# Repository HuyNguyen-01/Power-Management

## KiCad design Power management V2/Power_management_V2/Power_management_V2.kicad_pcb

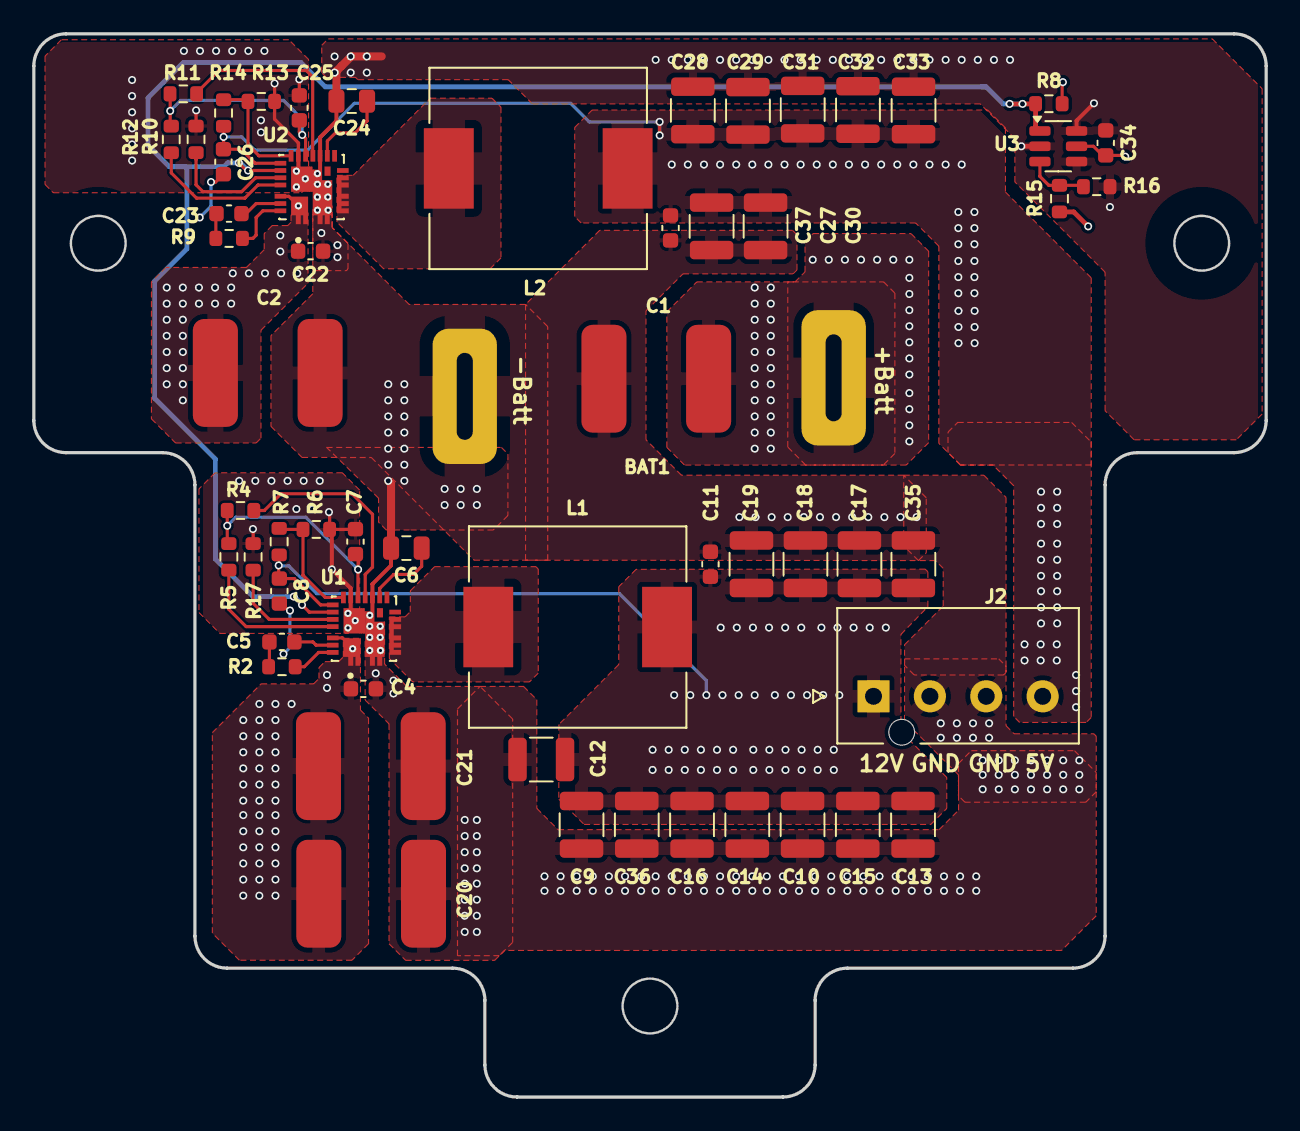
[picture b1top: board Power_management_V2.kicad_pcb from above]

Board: 4 copper layers, 76.5 x 66.0 mm, 60 parts (0 on the bottom side), 28 nets.

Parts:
BAT1: Conn_01x02; Milwaukee 18V battery connector R1
C1, C2, C20, C21: 22u/50V/3025; C_CER_7.5x6.3
C4, C5, C8, C11, C22, C23, C26, C34, C37: 100n/50V/0603; C_0603_1608Metric
C6, C24: 4.7u/50V/0805; C_0805_2012Metric
C7, C25: 1u/50V/0603; C_0603_1608Metric
C9, C10, C12, C13, C14, C15, C16, C17, C18, C19, C27, C28, C29, C30, C31, C32, C33, C35, C36: 22u/25V/1210; C_1210_3225Metric
J2: 1722861104; MOLEX_1722861104
L1, L2: 2.2u/22A; IND_SRP1265A-2R2M
NT1, NT2: NetTie_2; NetTie-2_SMD_Pad1.56mm
R2, R9: 2.2R/0603; R_0603_1608Metric
R4, R5, R8, R11, R12: 100k/0603; R_0603_1608Metric
R6, R13: 10k/0603/0.1%; R_0603_1608Metric
R7: 191K/0603/0.1%; R_0603_1608Metric
R10, R17: 200k/0603; R_0603_1608Metric
R14: 73.2K/0603/0.1; R_0603_1608Metric
R15: 2M/0603; R_0603_1608Metric
R16: 51.1K/0603; R_0603_1608Metric
U1, U2: SIC437AED; VREG_SIC437AED-T1-GE3
U3: TPS3711DDCR; TSOT-23-6

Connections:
+BATT: BAT1.1, C1.1, C2.1, C4.2, C20.1, C21.1, C22.2, C34.2, R8.2, R15.2, U1.1 (VIN), U1.22 (VIN), U2.1 (VIN), U2.22 (VIN), U3.5 (VDD)
/12V/EN_12V: R8.1, U1.19 (EN), U2.19 (EN), U3.1 (OUT)
/+5V: C26.2, C27.1, C28.1, C29.1, C30.1, C31.1, C32.1, C33.1, C37.2, J2.4, L2.2, R14.2, U2.18 (VOUT)
/+12V: C8.2, C9.1, C10.1, C11.2, C12.1, C13.1, C14.1, C15.1, C16.1, C17.1, C18.1, C19.1, C35.1, C36.1, J2.1, L1.2, R7.2, U1.18 (VOUT)
GND: BAT1.2, C1.2, C2.2, C4.1, C6.2, C8.1, C9.2, C10.2, C11.1, C12.2, C13.2, C14.2, C15.2, C16.2, C17.2, C18.2, C19.2, C20.2, C21.2, C22.1, C24.2, C26.1, C27.2, C28.2, C29.2, C30.2, C31.2, C32.2, C33.2, C34.1, C35.2, C36.2, C37.1, J2.2, J2.3, NT1.2, NT2.2, R16.1, U1.3 (PGND), U1.13 (PGND), U2.3 (PGND), U2.13 (PGND), U3.2 (GND-2), U3.4 (GND-4), U3.6 (GND-6)
GND1: C25.2, NT1.1, R10.2, R13.1, U2.16 (AGND), U2.25 (AGND)
GND2: C7.2, NT2.1, R6.1, R17.2, U1.16 (AGND), U1.25 (AGND)
unnamed: C5.2, R2.2
unnamed: C23.2, R9.2
unnamed: L1.1, U1.5 (SW)
unnamed: L2.1, U2.5 (SW)
unnamed: C5.1, U1.23 (BOOT)
unnamed: R6.2, R7.1, U1.17 (FB)
unnamed: R5.2, U1.21 (MODE1)
unnamed: R17.1, U1.20 (MODE2)
unnamed: R4.1, U1.14 (PGOOD)
unnamed: R2.1, U1.24 (PHASE)
unnamed: C7.1, R4.2, R5.1, U1.15 (VDD)
unnamed: C6.1, U1.12 (VDRV)
unnamed: C23.1, U2.23 (BOOT)
unnamed: R13.2, R14.1, U2.17 (FB)
unnamed: R12.2, U2.21 (MODE1)
unnamed: R10.1, U2.20 (MODE2)
unnamed: R11.1, U2.14 (PGOOD)
unnamed: R9.1, U2.24 (PHASE)
unnamed: C25.1, R11.2, R12.1, U2.15 (VDD)
unnamed: C24.1, U2.12 (VDRV)
unnamed: R15.1, R16.2, U3.3 (SENSE)

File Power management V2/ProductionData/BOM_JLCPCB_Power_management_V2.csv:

Designator,Quantity,Comment,Footprint,JLCPCB Part #
,,,,
"C1,C2,C20,C21",4,22u/50V/3025,Library:C_CER_7.5x6.3,C508864
"C4,C5,C8,C11,C22,C23,C26,C34,C37",9,100n/50V/0603,Capacitor_SMD:C_0603_1608Metric,C3011652
"C6,C24",2,4.7u/50V/0805,Capacitor_SMD:C_0805_2012Metric,C437557
"C7,C25",2,1u/50V/0603,Capacitor_SMD:C_0603_1608Metric,C5199872
"C9,C10,C12,C13,C14,C15,C16,C17,C18,C19,C27,C28,C29,C30,C31,C32,C33,C35,C36",19,22u/25V/1210,Capacitor_SMD:C_1210_3225Metric,C52306
J2,1,1722861104,Library:MOLEX_1722861104,C586647
"L1,L2",2,2.2u/22A,Library:IND_SRP1265A-2R2M,C2831487
,,,,
"R2,R9",2,2.2R/0603,Resistor_SMD:R_0603_1608Metric,C144672
"R4,R5,R8,R11,R12",5,100k/0603,Resistor_SMD:R_0603_1608Metric,C14675
"R6,R13",2,10k/0603/0.1%,Resistor_SMD:R_0603_1608Metric,C95204
R7,1,191K/0603/0.1%,Resistor_SMD:R_0603_1608Metric,C861179
"R10,R17",2,200k/0603,Resistor_SMD:R_0603_1608Metric,C105574
R14,1,73.2K/0603/0.1,Resistor_SMD:R_0603_1608Metric,C862276
R15,1,2M/0603,Resistor_SMD:R_0603_1608Metric,C114615
R16,1,51.1K/0603,Resistor_SMD:R_0603_1608Metric,C364359
"U1,U2",2,SIC437AED,Library:VREG_SIC437AED-T1-GE3,C2071432
U3,1,TPS3711DDCR,Package_TO_SOT_SMD:TSOT-23-6,C2877180

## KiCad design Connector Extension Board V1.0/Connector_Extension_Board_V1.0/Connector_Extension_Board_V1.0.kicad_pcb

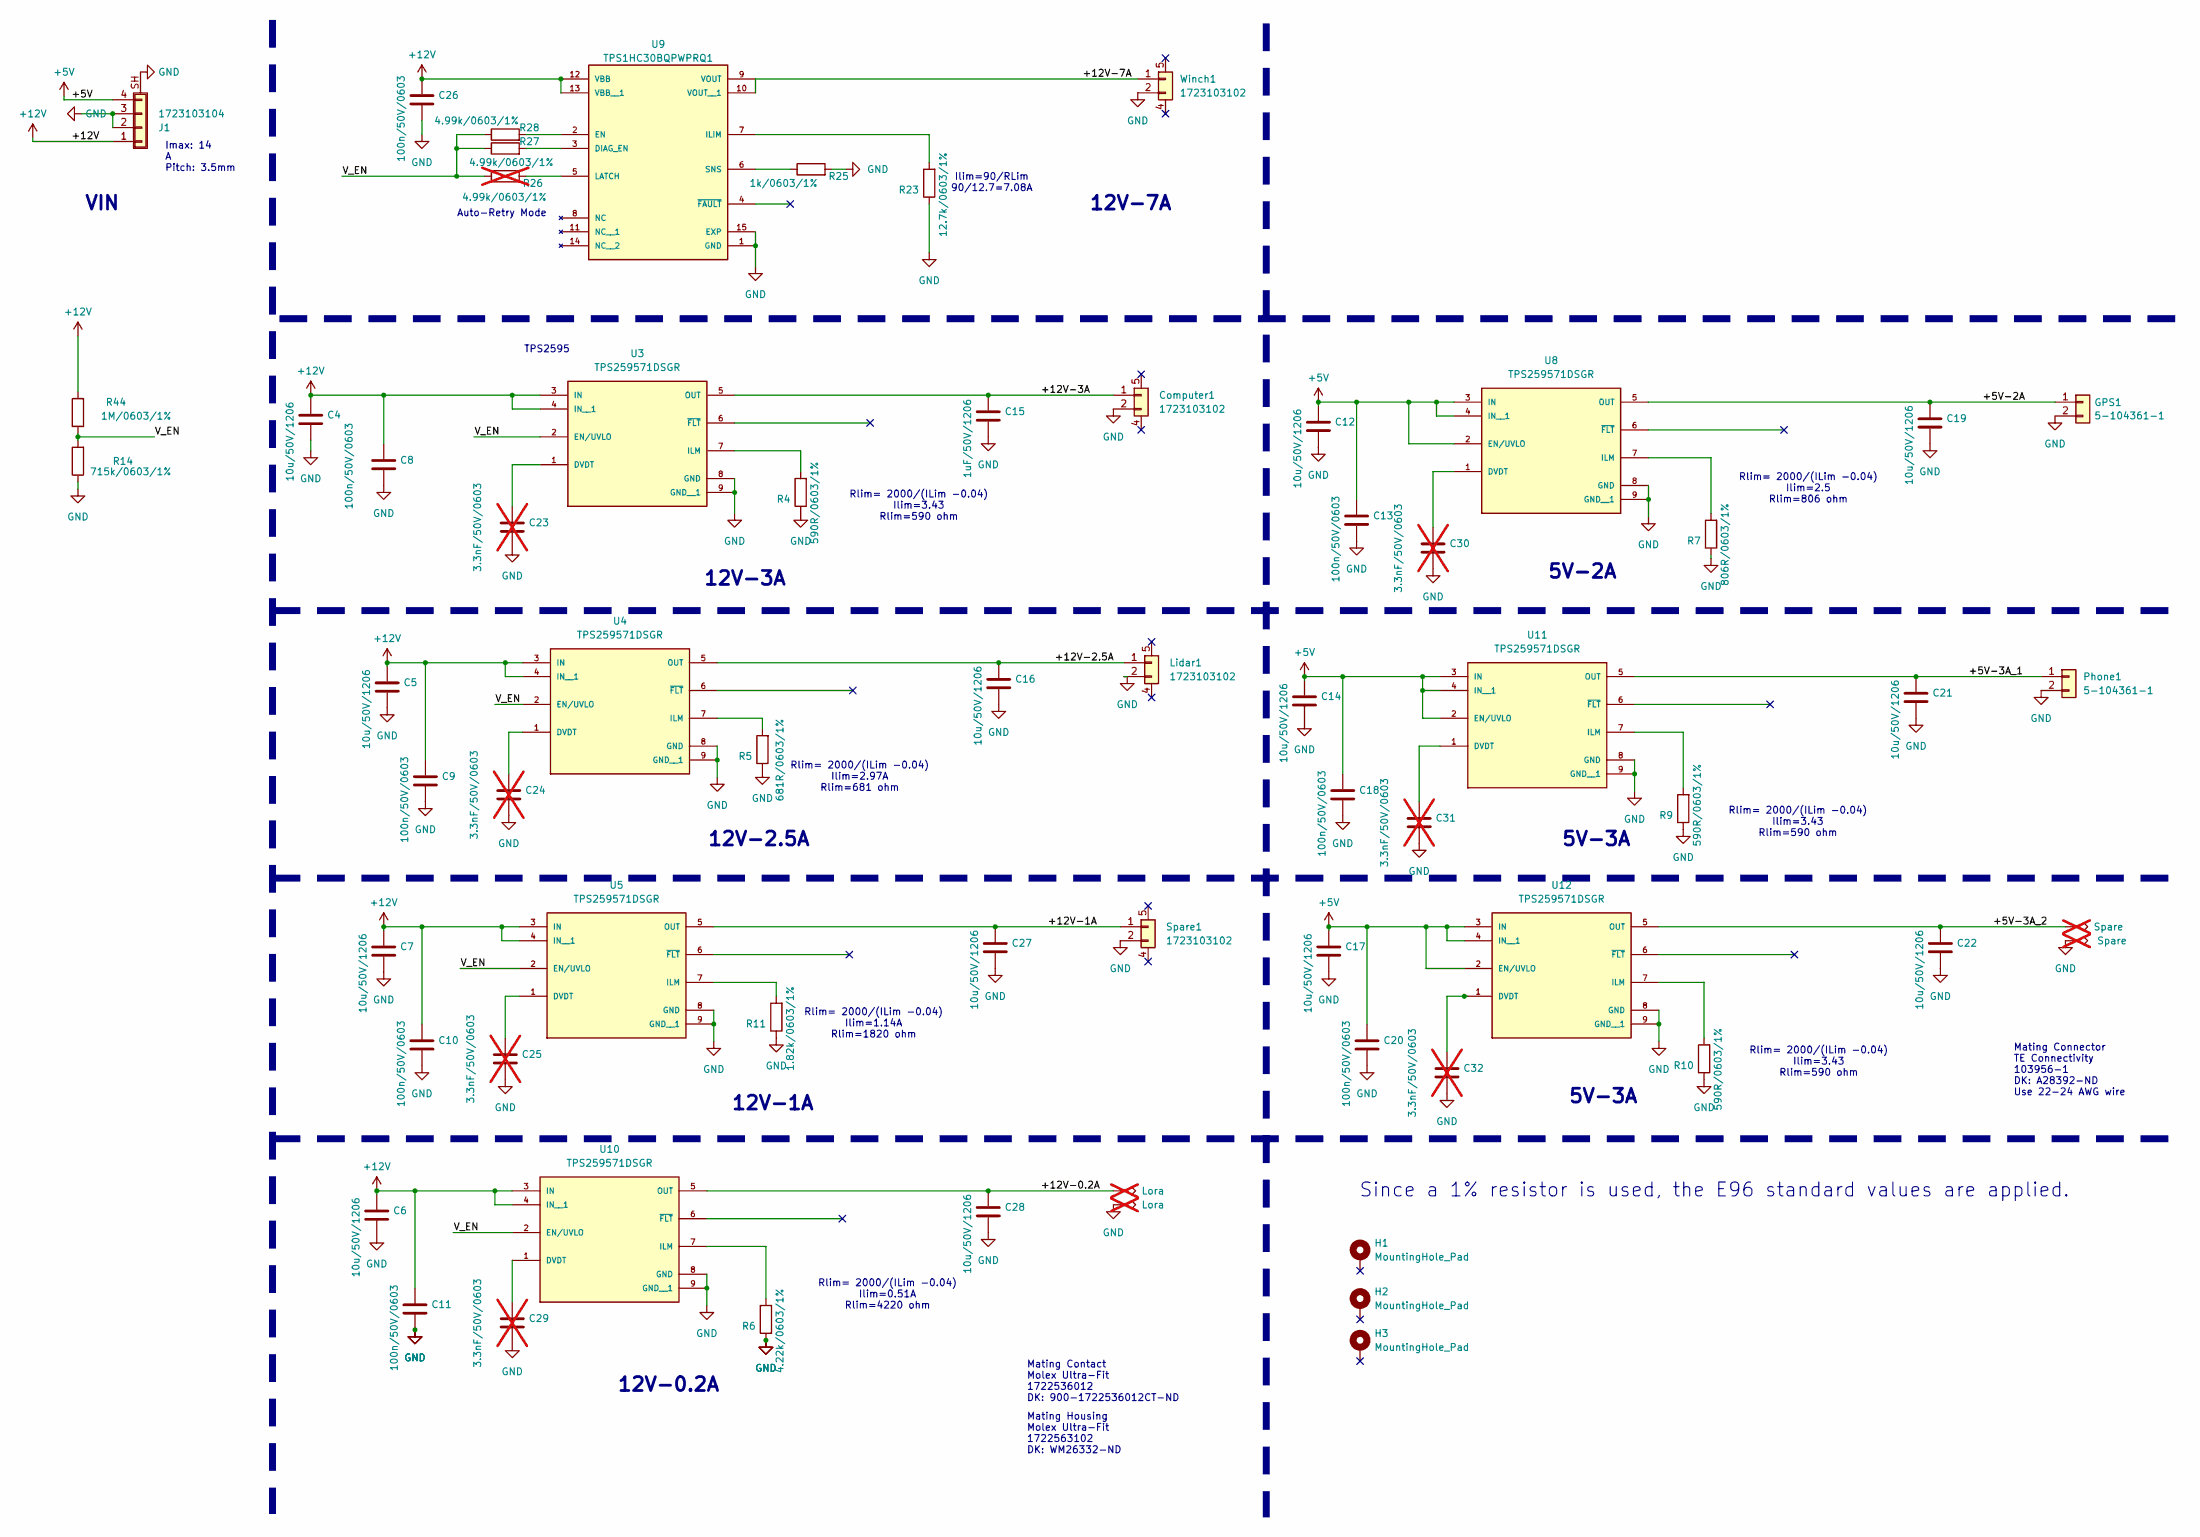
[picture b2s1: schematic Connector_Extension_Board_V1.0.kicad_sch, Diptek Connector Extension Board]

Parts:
C4, C5, C6, C7, C12, C14, C16, C17, C19, C21, C22, C27, C28: 10u/50V/1206; C_1206_3216Metric; Digikey 1276-2876-1-ND
C8, C9, C10, C11, C13, C18, C20, C26: 100n/50V/0603; C_0603_1608Metric; Digikey 587-1243-1-ND
C15: 1uF/50V/1206; C_1206_3216Metric; Digikey 1276-1068-1-ND
C23, C24, C25, C29, C30, C31, C32: 3.3nF/50V/0603; C_0603_1608Metric; Digikey NC; not fitted
Computer1: 1723103102; MOLEX_1723103102; Part 1723102202; Digikey 900-1723103102-ND
GPS1: 5-104361-1; TE_5-104361-1; Part 5-104361-1; Digikey A33961-ND
H1, H2, H3: MountingHole_Pad; MountingHole_3.1-5.8; Digikey NC
J1: 1723103104; MOLEX_1723103104; DIGIKEY 900-1723103104-ND
Lidar1: 1723103102; MOLEX_1723103102; Part 1723102202; Digikey 900-1723103102-ND
Phone1: 5-104361-1; TE_5-104361-1; Part 5-104361-1; Digikey A33961-ND
R4, R9, R10: 590R/0603/1%; R_0603_1608Metric; Digikey 311-590HRCT-ND
R5: 681R/0603/1%; R_0603_1608Metric; Digikey RMCF0603FT681RCT-ND
R6: 4.22k/0603/1%; R_0603_1608Metric; Digikey 311-4.22KHRCT-ND
R7: 806R/0603/1%; R_0603_1608Metric; Digikey P806HCT-ND
R11: 1.82k/0603/1%; R_0603_1608Metric; Digikey 311-1.82KHRCT-ND
R14: 715k/0603/1%; R_0603_1608Metric; Digikey 311-715KHRCT-ND
R23: 12.7k/0603/1%; R_0603_1608Metric; Digikey P12.7HCT-ND
R25: 1k/0603/1%; R_0603_1608Metric; Digikey RMCF0603FT1K00CT-ND
R26: 4.99k/0603/1%; R_0603_1608Metric; Digikey NC; not fitted
R27, R28: 4.99k/0603/1%; R_0603_1608Metric; Digikey RMCF0603FT4K99CT-ND
R44: 1M/0603/1%; R_0603_1608Metric; Digikey P1.00MHCT-ND
Spare1: 1723103102; MOLEX_1723103102; Part 1723102202; Digikey 900-1723103102-ND
TP1, TP2: Lora; TestPoint_Loop_D2.50mm_Drill1.0mm; not fitted
TP3, TP4: Spare; TestPoint_Loop_D2.50mm_Drill1.0mm; not fitted
U3, U4, U5, U8, U10, U11, U12: TPS259571DSGR; SON50P200X200X80-9N; DIGIKEY 296-50500-1-ND
U9: TPS1HC30BQPWPRQ1; IC_TPS1HC30BQPWPRQ1; DIGIKEY 296-TPS1HC30BQPWPRQ1CT-ND
Winch1: 1723103102; MOLEX_1723103102; Part 1723102202; Digikey 900-1723103102-ND

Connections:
+5V: C12.1, C13.1, C14.1, C17.1, C18.1, C20.1, J1.4, U8.2 (EN/UVLO), U8.3 (IN), U8.4 (IN__1), U11.2 (EN/UVLO), U11.3 (IN), U11.4 (IN__1), U12.2 (EN/UVLO), U12.3 (IN), U12.4 (IN__1)
+12V: C4.1, C5.1, C6.1, C7.1, C8.1, C9.1, C10.1, C11.1, C26.1, J1.1, R44.2, U3.3 (IN), U3.4 (IN__1), U4.3 (IN), U4.4 (IN__1), U5.3 (IN), U5.4 (IN__1), U9.12 (VBB), U9.13 (VBB__1), U10.3 (IN), U10.4 (IN__1)
/+5V-2A: C19.1, GPS1.1, U8.5 (OUT)
/+5V-3A_1: C21.1, Phone1.1, U11.5 (OUT)
/+5V-3A_2: C22.1, TP3.1, U12.5 (OUT)
/+12V-0.2A: C28.1, TP1.1, U10.5 (OUT)
/+12V-1A: C27.1, Spare1.1, U5.5 (OUT)
/+12V-2.5A: C16.1, Lidar1.1, U4.5 (OUT)
/+12V-3A: C15.1, Computer1.1, U3.5 (OUT)
/+12V-7A: U9.9 (VOUT), U9.10 (VOUT__1), Winch1.1
/V_EN: R14.2, R26.1, R27.1, R28.1, R44.1, U3.2 (EN/UVLO), U4.2 (EN/UVLO), U5.2 (EN/UVLO), U10.2 (EN/UVLO)
GND: C4.2, C5.2, C6.2, C7.2, C8.2, C9.2, C10.2, C11.2, C12.2, C13.2, C14.2, C15.2, C16.2, C17.2, C18.2, C19.2, C20.2, C21.2, C22.2, C23.2, C24.2, C25.2, C26.2, C27.2, C28.2, C29.2, C30.2, C31.2, C32.2, Computer1.2, GPS1.2, J1.2, J1.3, J1.SH (Shield), Lidar1.2, Phone1.2, R4.1, R5.1, R6.1, R7.1, R9.1, R10.1, R11.1, R14.1, R23.1, R25.2, Spare1.2, TP2.1, TP4.1, U3.8 (GND), U3.9 (GND__1), U4.8 (GND), U4.9 (GND__1), U5.8 (GND), U5.9 (GND__1), U8.8 (GND), U8.9 (GND__1), U9.1 (GND), U9.15 (EXP), U10.8 (GND), U10.9 (GND__1), U11.8 (GND), U11.9 (GND__1), U12.8 (GND), U12.9 (GND__1), Winch1.2
unnamed: C23.1, U3.1 (DVDT)
unnamed: R4.2, U3.7 (ILM)
unnamed: C24.1, U4.1 (DVDT)
unnamed: R5.2, U4.7 (ILM)
unnamed: C25.1, U5.1 (DVDT)
unnamed: R11.2, U5.7 (ILM)
unnamed: C30.1, U8.1 (DVDT)
unnamed: R7.2, U8.7 (ILM)
unnamed: R27.2, U9.3 (DIAG_EN)
unnamed: R28.2, U9.2 (EN)
unnamed: R23.2, U9.7 (ILIM)
unnamed: R26.2, U9.5 (LATCH)
unnamed: R25.1, U9.6 (SNS)
unnamed: C29.1, U10.1 (DVDT)
unnamed: R6.2, U10.7 (ILM)
unnamed: C31.1, U11.1 (DVDT)
unnamed: R9.2, U11.7 (ILM)
unnamed: C32.1, U12.1 (DVDT)
unnamed: R10.2, U12.7 (ILM)

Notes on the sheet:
5V-3A
12V-3A
Mating Connector TE Connectivity 103956-1 DK: A28392-ND Use 22-24 AWG wire
12V-1A
TPS2595
Rlim= 2000/(ILim -0.04) Ilim=1.14A Rlim=1820 ohm
Mating Housing Molex Ultra-Fit 1722563102 DK: WM26332-ND
12V-7A
Rlim= 2000/(ILim -0.04) Ilim=2.97A Rlim=681 ohm
5V-2A
12V-2.5A
Since a 1% resistor is used, the E96 standard values are applied.
Rlim= 2000/(ILim -0.04) Ilim=2.5 Rlim=806 ohm
Auto-Retry Mode
Imax: 14 A Pitch: 3.5mm
Rlim= 2000/(ILim -0.04) Ilim=3.43 Rlim=590 ohm
Mating Contact Molex Ultra-Fit 1722536012 DK: 900-1722536012CT-ND
VIN
12V-0.2A
Ilim=90/RLim 90/12.7=7.08A
Rlim= 2000/(ILim -0.04) Ilim=0.51A Rlim=4220 ohm

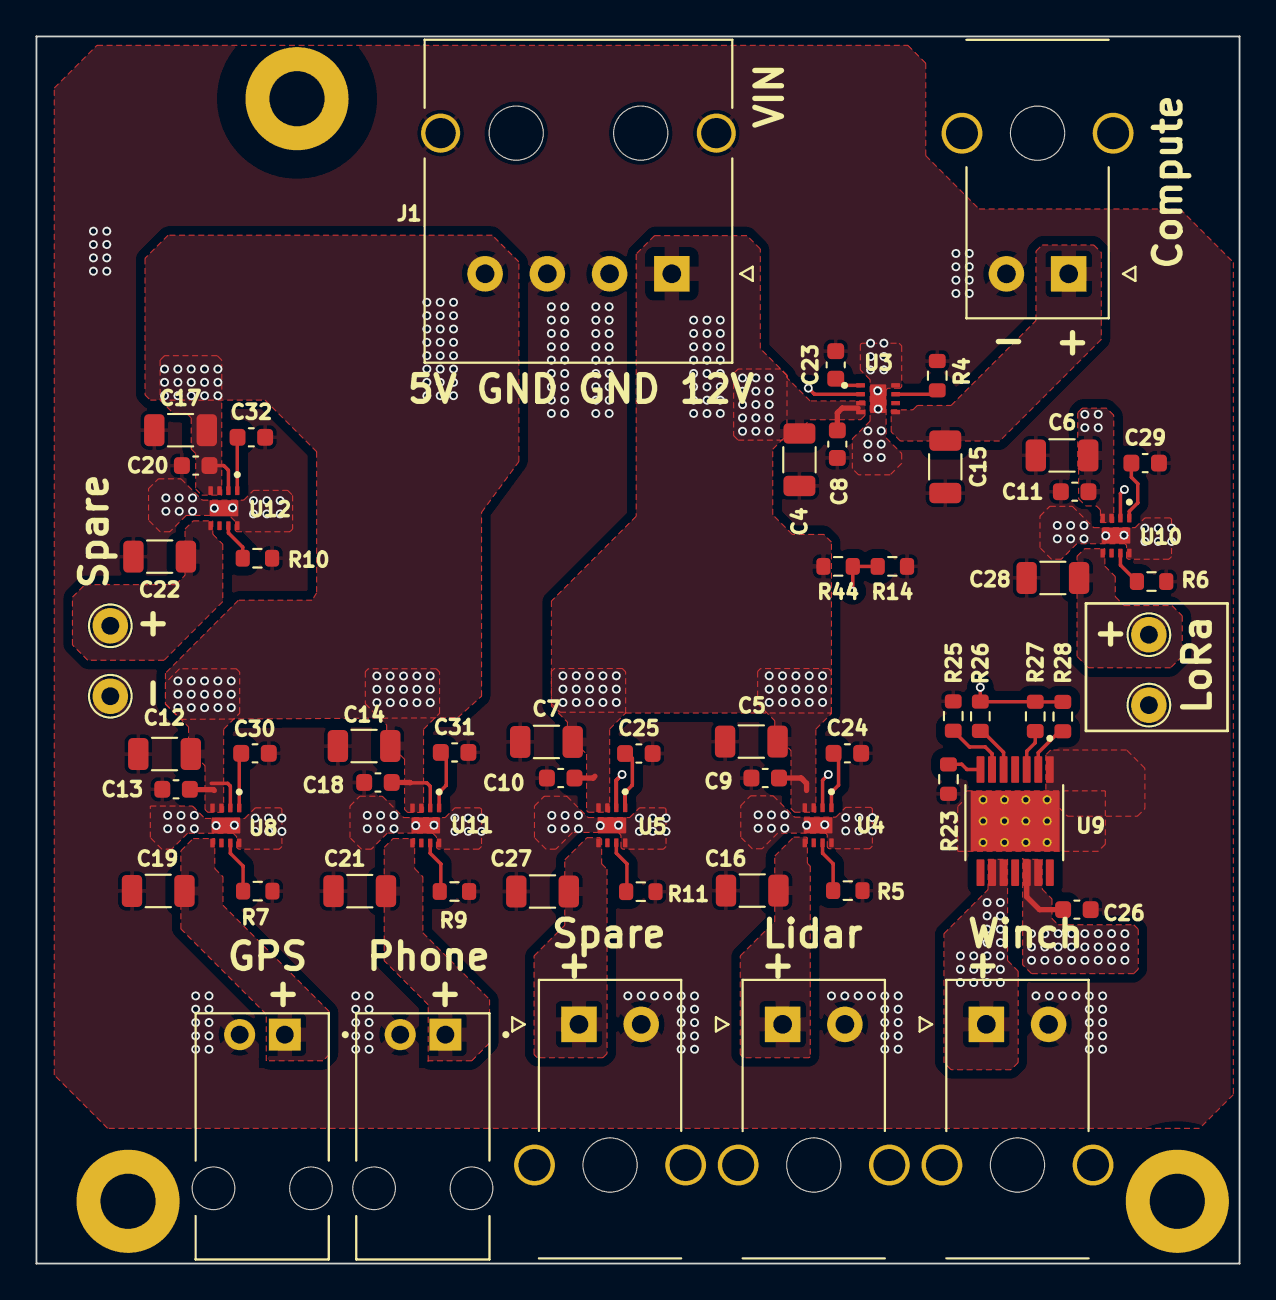
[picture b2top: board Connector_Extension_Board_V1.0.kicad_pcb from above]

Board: 4 copper layers, 67.7 x 69.0 mm, 65 parts (0 on the bottom side), 31 nets.

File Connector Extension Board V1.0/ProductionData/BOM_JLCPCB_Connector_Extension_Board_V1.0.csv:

Reference,Qty,Value,Footprint,JLCPCB Part #
"C4,C5,C6,C7,C12,C14,C16,C17,C19,C21,C22,C27,C28",13,10u/50V/1206,Capacitor_SMD:C_1206_3216Metric,C13585
"C8,C9,C10,C11,C13,C18,C20,C26",8,100n/50V/0603,Capacitor_SMD:C_0603_1608Metric,C3011652
C15,1,1uF/50V/1206,Capacitor_SMD:C_1206_3216Metric,C1848
"Computer1,Lidar1,Spare1,Winch1",4,1723103102,Library:MOLEX_1723103102,C17318087
"GPS1,Phone1",2,5-104361-1,Library:TE_5-104361-1,C5165817
J1,1,1723103104,Library:MOLEX_1723103104,C17628250
"R4,R9,R10",3,590R/0603/1%,Resistor_SMD:R_0603_1608Metric,C23084
R5,1,681R/0603/1%,Resistor_SMD:R_0603_1608Metric,C5126127
R6,1,4.22k/0603/1%,Resistor_SMD:R_0603_1608Metric,C23042
R7,1,806R/0603/1%,Resistor_SMD:R_0603_1608Metric,C23116
R11,1,1.82k/0603/1%,Resistor_SMD:R_0603_1608Metric,C273756
R14,1,715k/0603/1%,Resistor_SMD:R_0603_1608Metric,C137685
R23,1,12.7k/0603/1%,Resistor_SMD:R_0603_1608Metric,C138285
R25,1,1k/0603/1%,Resistor_SMD:R_0603_1608Metric,C22548
"R27,R28",2,4.99k/0603/1%,Resistor_SMD:R_0603_1608Metric,C114621
R44,1,1M/0603/1%,Resistor_SMD:R_0603_1608Metric,C105578
"U3,U4,U5,U8,U10,U11,U12",7,TPS259571DSGR,Library:SON50P200X200X80-9N,C471038
U9,1,TPS1HC30BQPWPRQ1,Library:IC_TPS1HC30BQPWPRQ1,C7496534

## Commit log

2025-12-18 Hoan thanh SCH mach Power
2025-12-19 Hoan thanh SCH lan 1
2025-12-24 Chỉnh sủa SCH 24/12
2025-12-26 Hoan thanh footprint
2025-12-29 hoan thanh sap xep
2025-12-29 Hoan thien Sap xep Linh kien
2026-01-12 Cập nhật connecter 12 5
2026-01-12 Cap nhat 12/1
2026-01-13 Hoan thanh chinh sua theo phan hoi 12/1
2026-01-20 Thay doi kich thuoc mach power
2026-01-22 Layout 2201
2026-01-23 Hoan thanh layout PCB Power
2026-01-23 Hoan thanh layout va BOM lisst
2026-02-03 Cap nhat chiu 3/2
2026-02-04 Hoan thanh chinh sua 4/2
2026-02-11 Cap nhat 11/2
2026-02-24 Cap Nhat 24/2
2026-02-24 Tao file nen de gui
2026-02-25 Thay doi JLCPCB Part J2
2026-02-25 Hoan thanh cap nhat ngay 25/2
2026-02-26 cap nhat 26/2
